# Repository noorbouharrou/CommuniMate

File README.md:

# CommuniMate

## Getting started

To make it easy for you to get started with GitLab, here's a list of recommended next steps.

Already a pro? Just edit this README.md and make it your own. Want to make it easy? [Use the template at the bottom](#editing-this-readme)!

## Add your files

- [ ] [Create](https://docs.gitlab.com/ee/user/project/repository/web_editor.html#create-a-file) or [upload](https://docs.gitlab.com/ee/user/project/repository/web_editor.html#upload-a-file) files
- [ ] [Add files using the command line](https://docs.gitlab.com/ee/gitlab-basics/add-file.html#add-a-file-using-the-command-line) or push an existing Git repository with the following command:

```
cd existing_repo
git remote add origin https://gitlab.cmi.hro.nl/1048112/communimate.git
git branch -M main
git push -uf origin main
```

## Integrate with your tools

- [ ] [Set up project integrations](https://gitlab.cmi.hro.nl/1048112/communimate/-/settings/integrations)

## Collaborate with your team

- [ ] [Invite team members and collaborators](https://docs.gitlab.com/ee/user/project/members/)
- [ ] [Create a new merge request](https://docs.gitlab.com/ee/user/project/merge_requests/creating_merge_requests.html)
- [ ] [Automatically close issues from merge requests](https://docs.gitlab.com/ee/user/project/issues/managing_issues.html#closing-issues-automatically)
- [ ] [Enable merge request approvals](https://docs.gitlab.com/ee/user/project/merge_requests/approvals/)
- [ ] [Set auto-merge](https://docs.gitlab.com/ee/user/project/merge_requests/merge_when_pipeline_succeeds.html)

## Test and Deploy

Use the built-in continuous integration in GitLab.

- [ ] [Get started with GitLab CI/CD](https://docs.gitlab.com/ee/ci/quick_start/index.html)
- [ ] [Analyze your code for known vulnerabilities with Static Application Security Testing (SAST)](https://docs.gitlab.com/ee/user/application_security/sast/)
- [ ] [Deploy to Kubernetes, Amazon EC2, or Amazon ECS using Auto Deploy](https://docs.gitlab.com/ee/topics/autodevops/requirements.html)
- [ ] [Use pull-based deployments for improved Kubernetes management](https://docs.gitlab.com/ee/user/clusters/agent/)
- [ ] [Set up protected environments](https://docs.gitlab.com/ee/ci/environments/protected_environments.html)

***

# Editing this README

When you're ready to make this README your own, just edit this file and use the handy template below (or feel free to structure it however you want - this is just a starting point!). Thanks to [makeareadme.com](https://www.makeareadme.com/) for this template.

## Suggestions for a good README

Every project is different, so consider which of these sections apply to yours. The sections used in the template are suggestions for most open source projects. Also keep in mind that while a README can be too long and detailed, too long is better than too short. If you think your README is too long, consider utilizing another form of documentation rather than cutting out information.

## Name
Choose a self-explaining name for your project.

## Description
Let people know what your project can do specifically. Provide context and add a link to any reference visitors might be unfamiliar with. A list of Features or a Background subsection can also be added here. If there are alternatives to your project, this is a good place to list differentiating factors.

## Badges
On some READMEs, you may see small images that convey metadata, such as whether or not all the tests are passing for the project. You can use Shields to add some to your README. Many services also have instructions for adding a badge.

## Visuals
Depending on what you are making, it can be a good idea to include screenshots or even a video (you'll frequently see GIFs rather than actual videos). Tools like ttygif can help, but check out Asciinema for a more sophisticated method.

## Installation
Within a particular ecosystem, there may be a common way of installing things, such as using Yarn, NuGet, or Homebrew. However, consider the possibility that whoever is reading your README is a novice and would like more guidance. Listing specific steps helps remove ambiguity and gets people to using your project as quickly as possible. If it only runs in a specific context like a particular programming language version or operating system or has dependencies that have to be installed manually, also add a Requirements subsection.

## Usage
Use examples liberally, and show the expected output if you can. It's helpful to have inline the smallest example of usage that you can demonstrate, while providing links to more sophisticated examples if they are too long to reasonably include in the README.

## Support
Tell people where they can go to for help. It can be any combination of an issue tracker, a chat room, an email address, etc.

## Roadmap
If you have ideas for releases in the future, it is a good idea to list them in the README.

## Contributing
State if you are open to contributions and what your requirements are for accepting them.

For people who want to make changes to your project, it's helpful to have some documentation on how to get started. Perhaps there is a script that they should run or some environment variables that they need to set. Make these steps explicit. These instructions could also be useful to your future self.

You can also document commands to lint the code or run tests. These steps help to ensure high code quality and reduce the likelihood that the changes inadvertently break something. Having instructions for running tests is especially helpful if it requires external setup, such as starting a Selenium server for testing in a browser.

## Authors and acknowledgment
Show your appreciation to those who have contributed to the project.

## License
For open source projects, say how it is licensed.

## Project status
If you have run out of energy or time for your project, put a note at the top of the README saying that development has slowed down or stopped completely. Someone may choose to fork your project or volunteer to step in as a maintainer or owner, allowing your project to keep going. You can also make an explicit request for maintainers.

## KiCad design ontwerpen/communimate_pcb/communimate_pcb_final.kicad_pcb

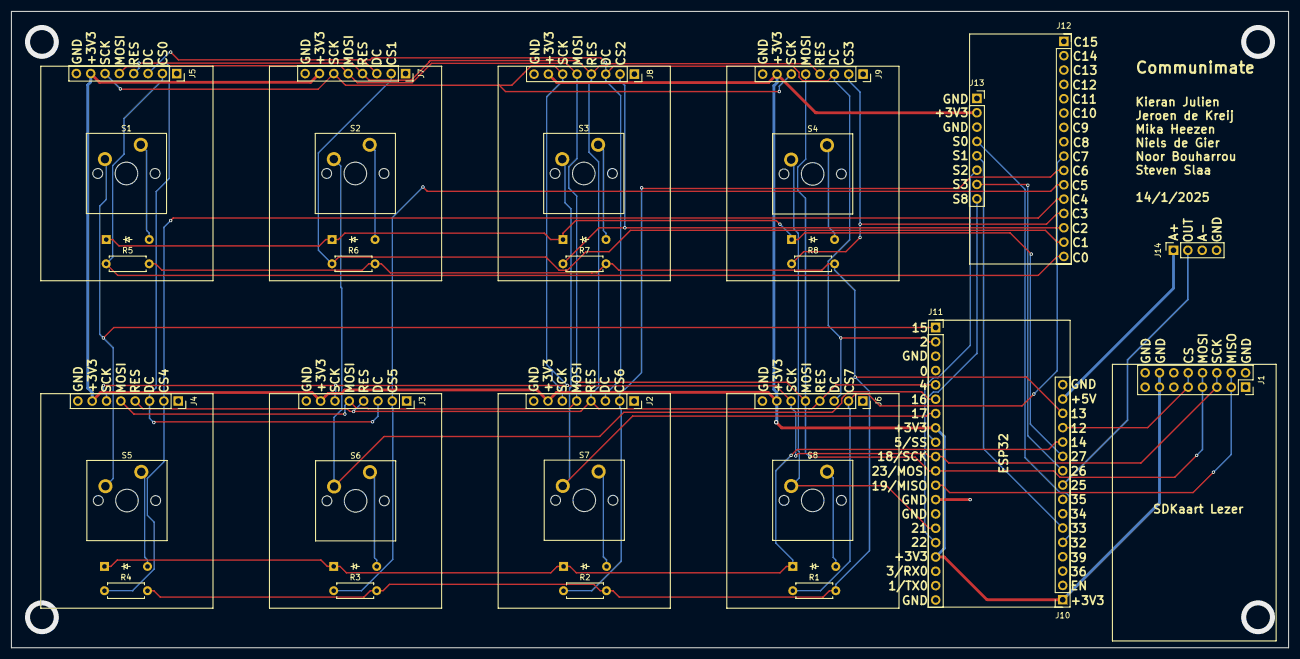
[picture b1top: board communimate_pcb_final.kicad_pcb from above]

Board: 2 copper layers, 226.2 x 112.7 mm, 38 parts (0 on the bottom side), 38 nets.

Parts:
D1, D2, D3, D4, D5, D6, D7, D8: Diode; Diode_DO-35
J1: Conn_02x08_Counter_Clockwise; PinSocket_2x08_P2.54mm_Vertical
J2, J3, J4, J5, J6, J7, J8, J9, J13: Conn_01x08; PinSocket_1x08_P2.54mm_Vertical
J10, J12: Conn_01x16; PinSocket_1x16_P2.54mm_Vertical
J11: Conn_01x20; PinSocket_1x20_P2.54mm_Vertical
J14: Conn_01x04; PinSocket_1x04_P2.54mm_Vertical
R1, R2, R3, R4, R5, R6, R7, R8: Resistor; R_Axial_DIN0207_L6.3mm_D2.5mm_P7.62mm_Horizontal
S1, S2, S3, S4, S5, S6, S7, S8: Keyswitch; MX_PCB_1.00u

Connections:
+3V3: J1.13, J1.14, J2.7, J3.7, J4.7, J5.7, J6.7, J7.7, J8.7, J9.7, J10.1, J11.8, J11.17, J13.2
+5V: J10.15, J14.1
AUDIO: J10.9, J14.2
Channel 0: J5.2, J12.16, R5.1
Channel 1: J7.2, J12.15, R6.1
Channel 2: J8.2, J12.14, R7.1
Channel 3: J9.2, J12.13, R8.1
Channel 4: J4.2, J12.12, R4.1
Channel 5: J3.2, J12.11, R3.1
Channel 6: J2.2, J12.10, R2.1
Channel 7: J6.2, J12.9, R1.1
Column 0: J11.1, S1.1, S5.1
Column 1: J11.6, S2.1, S6.1
Column 2: J11.7, S3.1, S7.1
Column 3: J11.15, S4.1, S8.1
DC: J2.3, J3.3, J4.3, J5.3, J6.3, J7.3, J8.3, J9.3, J11.2
GND: J1.1, J1.2, J1.15, J1.16, J2.8, J3.8, J4.8, J5.8, J6.8, J7.8, J8.8, J9.8, J10.16, J11.3, J11.13, J11.14, J11.20, J13.1, J13.3, J14.3, J14.4
MISO: J1.3, J1.4, J11.12
MOSI: J1.7, J1.8, J2.5, J3.5, J4.5, J5.5, J6.5, J7.5, J8.5, J9.5, J11.11
unnamed: D1.2 (A), S1.2
unnamed: D2.2 (A), S2.2
unnamed: D3.2 (A), S3.2
unnamed: D4.2 (A), S4.2
unnamed: D5.2 (A), S5.2
unnamed: D6.2 (A), S6.2
unnamed: D7.2 (A), S7.2
unnamed: D8.2 (A), S8.2
PULLUP: J10.14, R1.2, R2.2, R3.2, R4.2, R5.2, R6.2, R7.2, R8.2
RES: J2.4, J3.4, J4.4, J5.4, J6.4, J7.4, J8.4, J9.4, J11.5
Row 0: D1.1 (K), D2.1 (K), D3.1 (K), D4.1 (K), J10.11
Row 1: D5.1 (K), D6.1 (K), D7.1 (K), D8.1 (K), J10.12
S0: J10.5, J13.4
S1: J10.6, J13.5
S2: J11.16, J13.6
S3: J10.10, J13.7
SCK: J1.5, J1.6, J2.6, J3.6, J4.6, J5.6, J6.6, J7.6, J8.6, J9.6, J11.10
SCREENCS: J11.9, J13.8
SDCS: J1.9, J1.10, J10.13

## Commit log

2024-12-10 Added Basic display example
2024-12-10 added multiplexer example
2024-12-10 Added working multiplexer tft example
2024-12-10 Added comments and updated folder structure
2024-12-10 fixed typo
2024-12-10 updated code to display image
2024-12-17 Added demos for API
2024-12-17 new front-end
2024-12-19 example sdkaart met schermen en knoppen
2024-12-19 Update front-end
2025-01-14 change mp3 to wav
2025-01-14 add ffmpeg to dockerFile
2025-01-27 add text
2025-01-27 change the width and height
2025-01-27 Logo PNG en PSD toegevoegd
2025-01-31 reverse text
2025-01-31 make it download png
2025-01-31 test for png
2025-01-31 nog steeds png
2025-01-31 no longer png
2025-01-31 NO PNG
2025-01-31 hopelijk werkt dit
2025-01-31 change port
2025-01-31 Revert "change port"
    This reverts commit ed4a990d8213ae825fbc1492c535edf8e6d4b23d.
2025-01-31 Revert "hopelijk werkt dit"
    This reverts commit 854cff665a232029412dd8e74211d05bcc2717a9.
2025-01-31 Revert "NO PNG"
    This reverts commit e46a185492e490d021e3a0e7d39a254d0b75618a.
2025-01-31 Revert "no longer png"
    This reverts commit 39fc10f725bee493fc85cdb0637600f2950f18f6.
2025-01-31 Revert "nog steeds png"
    This reverts commit f1b638000dd66a9a1a8ce06449dcd12245fb56c2.
2025-01-31 Revert "test for png"
    This reverts commit d8eaed0eeec7e5a866b1ef9b614f756b3995dc16.
2025-01-31 Revert "png"
    This reverts commit f757fed04b171635037f550ebe98e568796ca508.
2025-01-31 Revert "make it download png"
    This reverts commit d7565d963193cd9b166dae3049ab9fd8e5ba6574.
2025-01-31 Revert "reverse text"
    This reverts commit 4bcc563b3bce89745f509d076a673ea29b567ab8.
2025-01-31 add ;
2025-01-31 buffer relocation
2025-02-05 latest fixes and styling
2025-02-07 Create maattekeningen
2025-02-07 Rename key_adapter_john.stl to key_adapter_V1.stl
2025-02-07 Create d
2025-02-09 Add main code
